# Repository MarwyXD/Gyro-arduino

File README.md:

# Gyro-arduino

# This file will contain arduino program and schematic with PCB of my gyroscope trying.

# I  wrote the program in such a way that depending on how much you tilt the gyroscope from its standard position, the light of the given LED diode will be directly proportional to it.

# Pins 3 to 8 on arduino nano are outputs for the LGB leds, you can reconfigure the pinout as you want, i used the wiring for the gyroscope as i founded on the internet datasheet for the gyroscope (+ i downloaded library for it)

# My model of gyroscope is GY-521.

# Thank you.

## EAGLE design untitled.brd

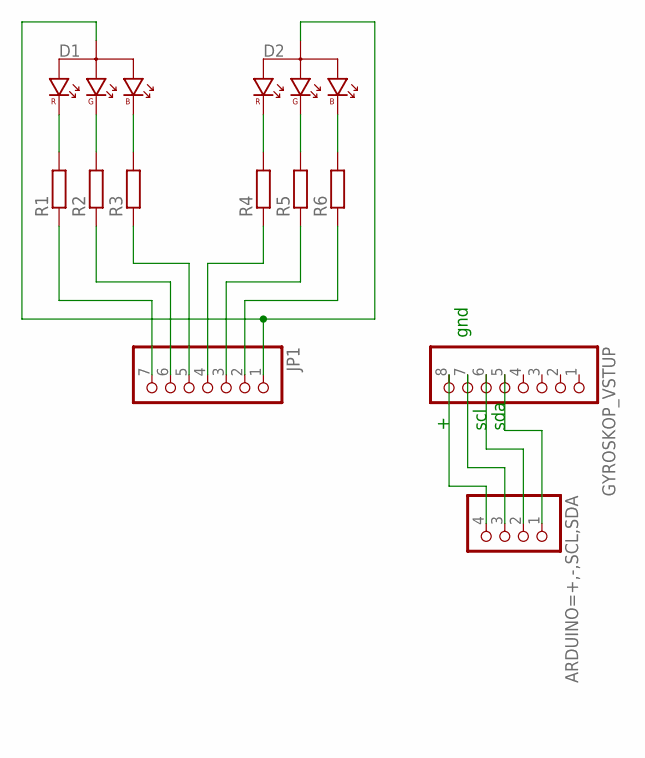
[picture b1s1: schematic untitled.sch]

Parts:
ARDUINO=+,-,SCL,SDA: PINHD-1X4; 1X04
D1, D2: LED_RGB; LED_5-RGB
GYROSKOP_VSTUP: PINHD-1X8; 1X08
JP1: PINHD-1X7; 1X07
R1, R2, R3, R4, R5, R6: R-EU_0207/10; 0207/10

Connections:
unnamed: D1.1 (R), R1.2
unnamed: D1.3 (G), R2.2
unnamed: D1.4 (B), R3.2
unnamed: JP1.5, R3.1
unnamed: JP1.6, R2.1
unnamed: JP1.7, R1.1
unnamed: D1.2 (A), D2.2 (A), JP1.1
unnamed: JP1.4, R4.1
unnamed: JP1.3, R5.1
unnamed: JP1.2, R6.1
unnamed: D2.1 (R), R4.2
unnamed: D2.3 (G), R5.2
unnamed: D2.4 (B), R6.2
unnamed: ARDUINO=+,-,SCL,SDA.4, GYROSKOP_VSTUP.8
unnamed: ARDUINO=+,-,SCL,SDA.3, GYROSKOP_VSTUP.7
unnamed: ARDUINO=+,-,SCL,SDA.2, GYROSKOP_VSTUP.6
unnamed: ARDUINO=+,-,SCL,SDA.1, GYROSKOP_VSTUP.5

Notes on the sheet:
gnd
scl
sda

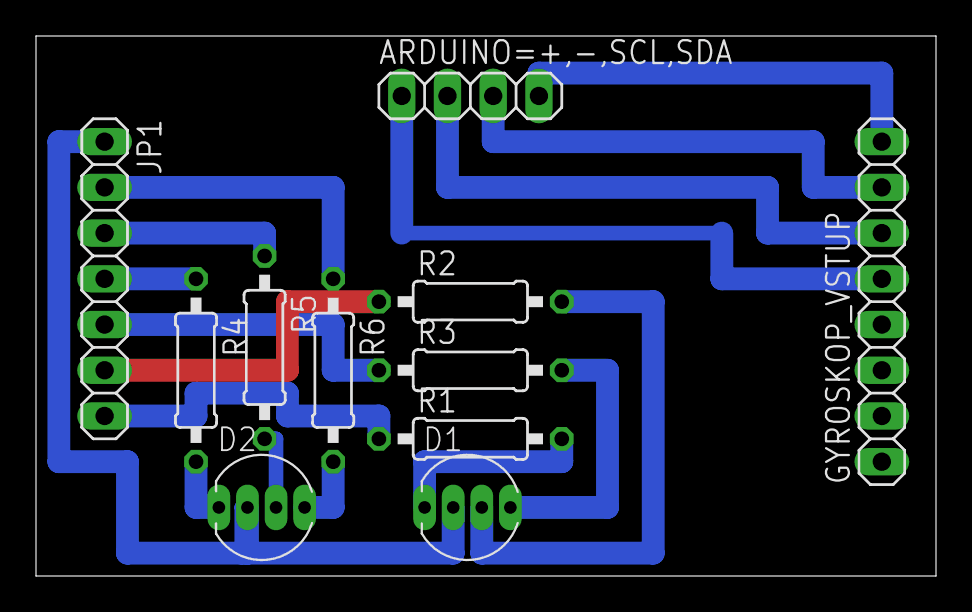
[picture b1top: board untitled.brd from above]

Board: 2 copper layers, 50.0 x 30.0 mm, 11 parts (0 on the bottom side), 17 nets.

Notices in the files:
parts and their libraries:
Copyright (C) PaJa 2001-2014
